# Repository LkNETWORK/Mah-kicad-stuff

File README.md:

# Mah-kicad-stuff
mah kicad shi

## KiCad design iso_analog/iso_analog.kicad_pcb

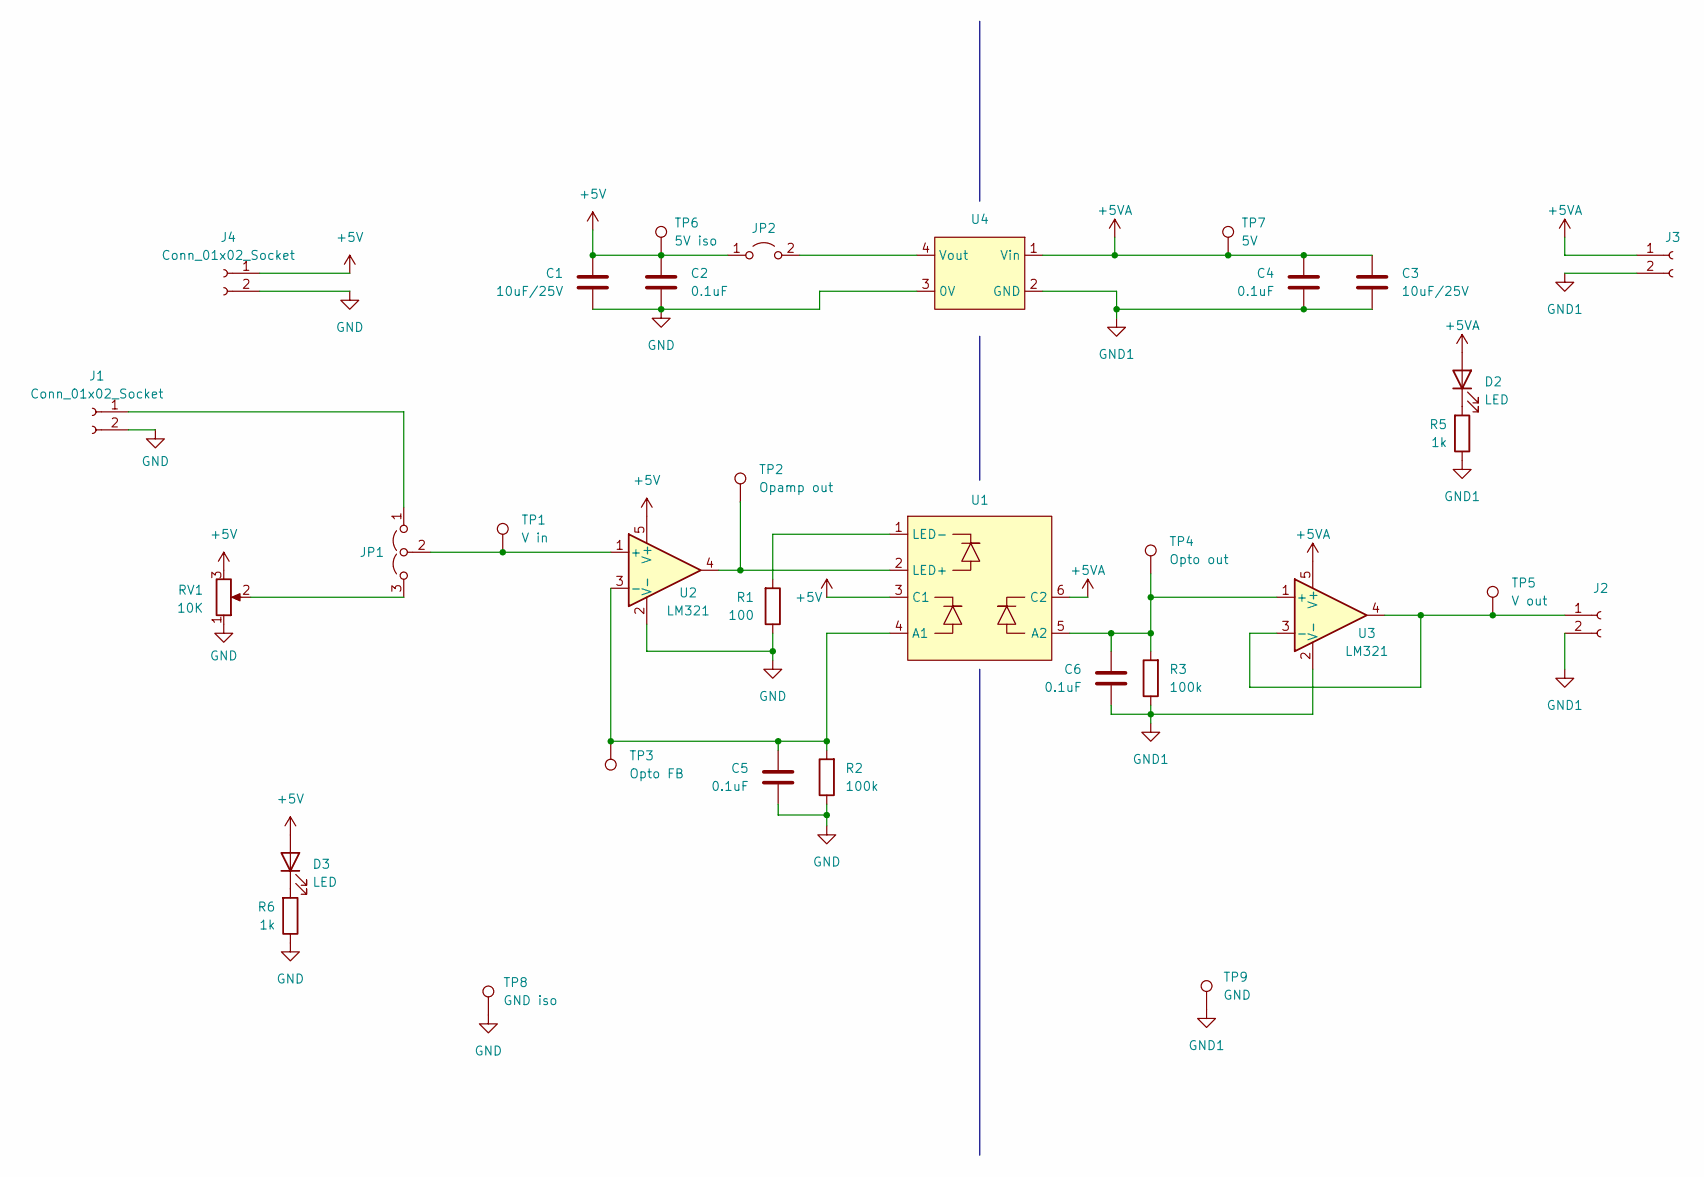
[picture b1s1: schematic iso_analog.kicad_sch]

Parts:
C1, C3: 10uF/25V; C_0805_2012Metric_Pad1.18x1.45mm_HandSolder_L
C2, C4, C5, C6: 0.1uF; C_0805_2012Metric_Pad1.18x1.45mm_HandSolder_L
D2, D3: LED; LED_0805_2012Metric_Pad1.45x1.40mm_HandSolder
J1, J2, J3, J4: Conn_01x02_Socket; PinHeader_1x02_P2.54mm_Vertical
JP1: Jumper_3_Open; SolderJumper-3_P1.3mm_Open_Pad1.0x1.5mm
JP2: Jumper_2_Open; SolderJumper-2_P1.3mm_Open_Pad1.0x1.5mm
R1: 100; R_0805_2012Metric_Pad1.20x1.40mm_HandSolder_L
R2, R3: 100k; R_0805_2012Metric_Pad1.20x1.40mm_HandSolder_L
R5, R6: 1k; R_0805_2012Metric_Pad1.20x1.40mm_HandSolder_L
RV1: 10K; BOURNS-3362P_pot
TP1: V in; PinHeader_1x01_P2.54mm_Vertical
TP2: Opamp out; TestPoint_Pad_D2.0mm
TP3: Opto FB; TestPoint_Pad_D2.0mm
TP4: Opto out; PinHeader_1x01_P2.54mm_Vertical
TP5: V out; TestPoint_Pad_D2.0mm
TP6: 5V iso; TestPoint_Pad_D2.0mm
TP7: 5V; TestPoint_Pad_D2.0mm
TP8: GND iso; PinHeader_1x01_P2.54mm_Vertical
TP9: GND; PinHeader_1x01_P2.54mm_Vertical
U1: LOC110P
U2, U3: LM321; SOT-23-5_HandSoldering
U4: B0505MT-1WR4

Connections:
+5V: C1.1, C2.1, D3.2 (A), J4.1, JP2.1 (A), RV1.3, TP6.1, U1.3 (C1), U2.5 (V+)
+5VA: C3.1, C4.1, D2.2 (A), J3.1, TP7.1, U1.6 (C2), U3.5 (V+), U4.1 (Vin)
GND: C1.2, C2.2, C5.2, J1.2, J4.2, R1.1, R2.1, R6.1, RV1.1, TP8.1, U2.2 (V-), U4.3 (0V)
GND1: C3.2, C4.2, C6.2, J2.2, J3.2, R3.1, R5.1, TP9.1, U3.2 (V-), U4.2 (GND)
unnamed: D2.1 (K), R5.2
unnamed: D3.1 (K), R6.2
unnamed: J1.1, JP1.1 (A)
unnamed: J2.1, TP5.1, U3.3 (-), U3.4
unnamed: JP1.3 (B), RV1.2
unnamed: JP1.2 (C), TP1.1, U2.1 (+)
unnamed: JP2.2 (B), U4.4 (Vout)
unnamed: C5.1, R2.2, TP3.1, U1.4 (A1), U2.3 (-)
unnamed: C6.1, R3.2, TP4.1, U1.5 (A2), U3.1 (+)
unnamed: TP2.1, U1.2 (LED+), U2.4
unnamed: R1.2, U1.1 (LED-)

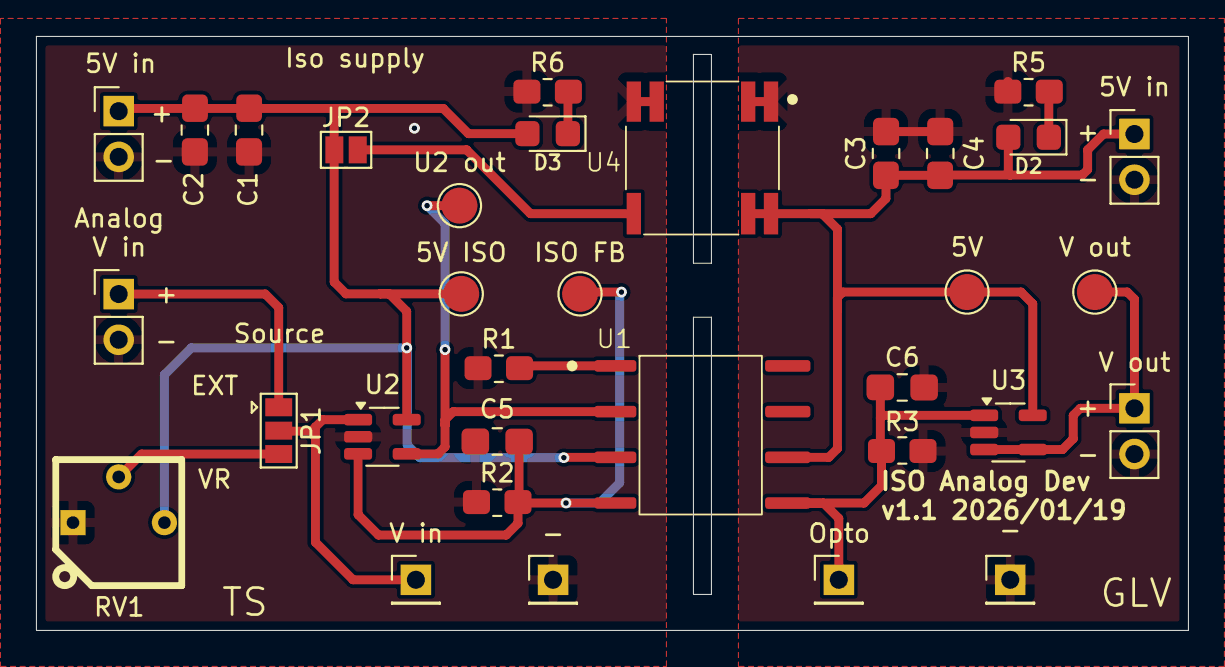
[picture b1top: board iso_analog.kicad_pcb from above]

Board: 2 copper layers, 64.0 x 33.0 mm, 33 parts (0 on the bottom side), 15 nets.

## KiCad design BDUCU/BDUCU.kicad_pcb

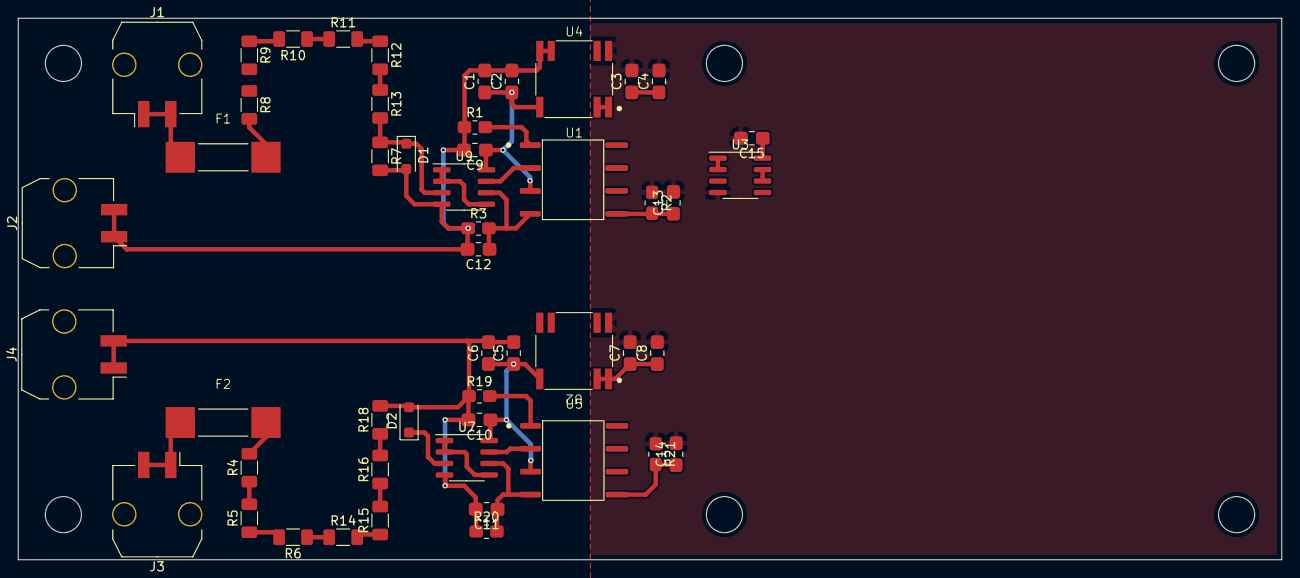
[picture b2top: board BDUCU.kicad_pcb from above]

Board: 2 copper layers, 139.9 x 60.0 mm, 50 parts (0 on the bottom side), 34 nets.

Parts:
C1, C4, C5, C8: 10uF/25V; C_0805_2012Metric_Pad1.18x1.45mm_HandSolder_L
C2, C3, C6, C7, C9, C10, C11, C12, C13, C14, C15: 0.1uF; C_0805_2012Metric_Pad1.18x1.45mm_HandSolder_L
D1, D2: BZT52B5V1; D_SOD-123F
F1, F2: Fuse; LittleFuse_462
J1, J2, J3, J4: Conn_01x02_Pin; Molex_Micro-Fit_3.0_43650-0210_1x02-1MP_P3.00mm_Horizontal
R1, R19: 1k; R_0805_2012Metric_Pad1.20x1.40mm_HandSolder_L
R2, R3, R20, R21: 10k; R_0805_2012Metric_Pad1.20x1.40mm_HandSolder_L
R4, R5, R6, R8, R9, R10, R11, R12, R13, R14, R15, R16: 210k; R_1206_3216Metric_Pad1.30x1.75mm_HandSolder
R7, R18: 10k; R_1206_3216Metric_Pad1.30x1.75mm_HandSolder
U1, U5: LOC110P
U2, U4: B0505MT-1WR4
U3, U7, U9: LM358; SOIC-8_3.9x4.9mm_P1.27mm

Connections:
+5V: C3.1, C4.1, C7.1, C8.1, C15.1, U1.6 (C2), U2.1 (Vin), U3.8 (V+), U4.1 (Vin), U5.6 (C2)
+5VL: C5.1, C6.1, C10.1, U2.4 (Vout), U5.3 (C1), U7.8 (V+)
+5VP: C1.1, C2.1, C9.1, U1.3 (C1), U4.4 (Vout), U9.8 (V+)
AC+: F1.1, R8.2
AC-: C1.2, C2.2, C9.2, C12.2, D1.2 (A), J2.1, J2.2, R1.1, R3.1, R7.2, U4.3 (0V), U9.4 (V-)
AC_ISO: U3.1, U3.2 (-)
GND: C3.2, C4.2, C7.2, C8.2, C13.2, C14.2, C15.2, R2.1, R21.1, U2.2 (GND), U3.4 (V-), U4.2 (GND)
unnamed: D1.1 (K), R7.1, R13.2, U9.3 (+)
unnamed: D2.1 (K), R16.2, R18.1, U7.3 (+)
unnamed: F1.2, J1.1, J1.2
unnamed: F2.2, J3.1, J3.2
unnamed: R4.1, R5.2
unnamed: R5.1, R6.2
unnamed: R8.1, R9.2
unnamed: R10.1, R11.1
unnamed: R9.1, R10.2
unnamed: R11.2, R12.1
unnamed: R12.2, R13.1
unnamed: R6.1, R14.1
unnamed: R14.2, R15.1
unnamed: R15.2, R16.1
unnamed: C12.1, R3.2, U1.4 (A1), U9.6 (-)
unnamed: C13.1, R2.2, U1.5 (A2), U3.3 (+)
unnamed: U1.2 (LED+), U9.7
unnamed: R1.2, U1.1 (LED-)
unnamed: C14.1, R21.2, U3.5 (+), U5.5 (A2)
unnamed: C11.1, R20.2, U5.4 (A1), U7.6 (-)
unnamed: U5.2 (LED+), U7.7
unnamed: R19.2, U5.1 (LED-)
unnamed: U7.1, U7.2 (-), U7.5 (+)
unnamed: U9.1, U9.2 (-), U9.5 (+)
TS+: F2.1, R4.2
TS-: C5.2, C6.2, C10.2, C11.2, D2.2 (A), J4.1, J4.2, R18.2, R19.1, R20.1, U2.3 (0V), U7.4 (V-)
TS_ISO: U3.6 (-), U3.7

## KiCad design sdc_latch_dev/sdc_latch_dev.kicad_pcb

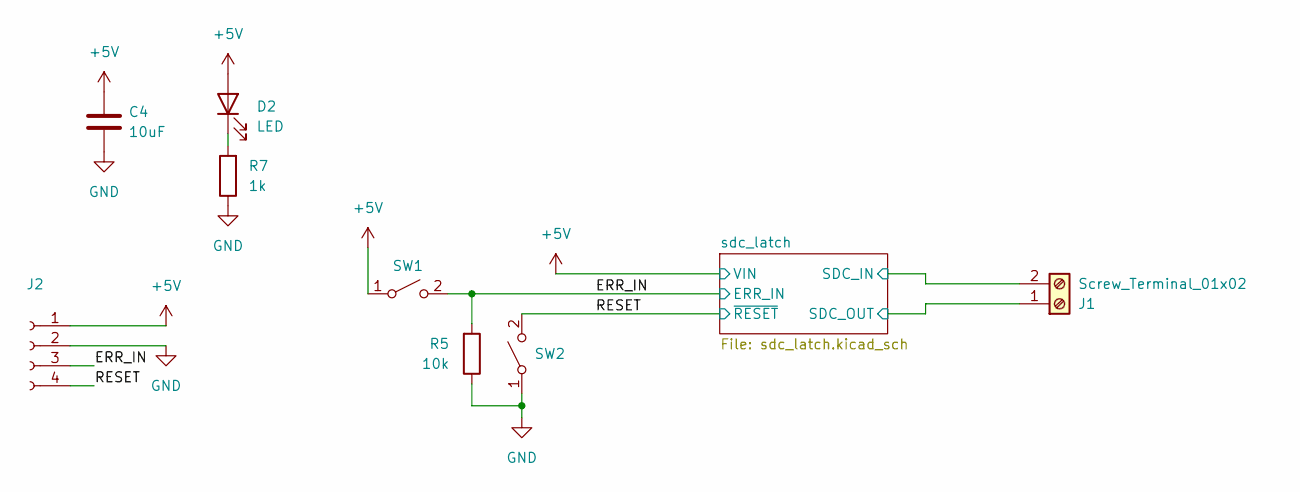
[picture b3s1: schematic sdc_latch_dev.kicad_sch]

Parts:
C4: 10uF; C_0805_2012Metric_Pad1.18x1.45mm_HandSolder_L
D2: LED; LED_0805_2012Metric_Pad1.15x1.40mm_HandSolder
J1: Screw_Terminal_01x02; TerminalBlock_Phoenix_MKDS-1,5-2_1x02_P5.00mm_Horizontal
J2: Conn_01x04_Socket; PinHeader_1x04_P2.54mm_Vertical
R5: 10k; R_0805_2012Metric_Pad1.20x1.40mm_HandSolder_L
R7: 1k; R_0805_2012Metric_Pad1.20x1.40mm_HandSolder_L
SW1, SW2: SW_SPST; SW_PUSH_6mm_H13mm

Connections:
+5V: C4.1, D2.2 (A), J2.1, SW1.1 (A); also elsewhere on the board
/ERR_IN: J2.3, R5.2, SW1.2 (B); also elsewhere on the board
/RESET: J2.4, SW2.2 (B); also elsewhere on the board
/sdc_latch/SDC_IN: J1.2; also elsewhere on the board
/sdc_latch/SDC_OUT: J1.1; also elsewhere on the board
GND: C4.2, J2.2, R5.1, R7.1, SW2.1 (A); also elsewhere on the board
unnamed: D2.1 (K), R7.2

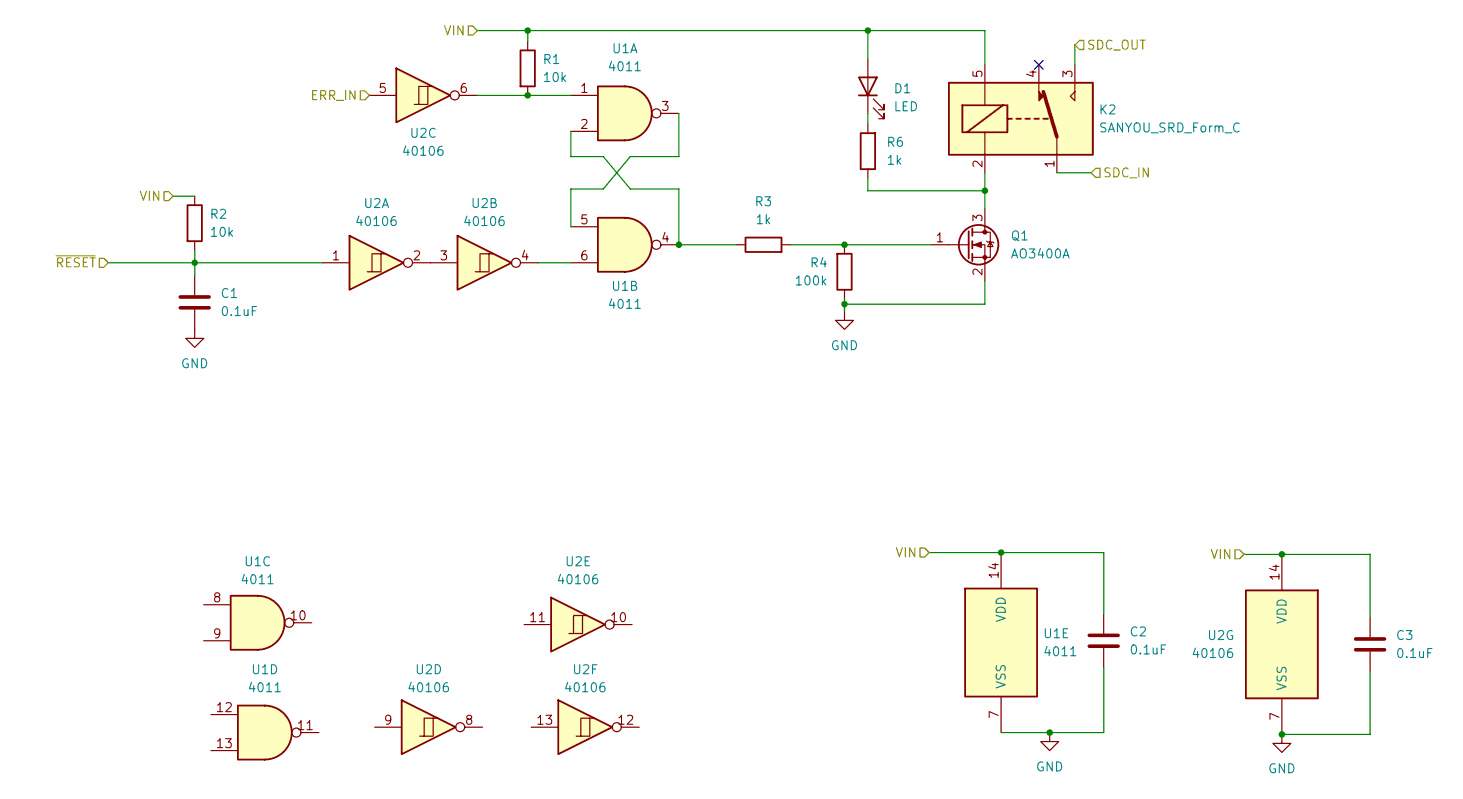
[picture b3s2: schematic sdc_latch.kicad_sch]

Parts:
C1, C2, C3: 0.1uF; C_0805_2012Metric_Pad1.18x1.45mm_HandSolder_L
D1: LED; LED_0805_2012Metric_Pad1.15x1.40mm_HandSolder
K2: SANYOU_SRD_Form_C; Relay_SPDT_SANYOU_SRD_Series_Form_C
Q1: AO3400A; SOT-23_Handsoldering
R1, R2: 10k; R_0805_2012Metric_Pad1.20x1.40mm_HandSolder_L
R3, R6: 1k; R_0805_2012Metric_Pad1.20x1.40mm_HandSolder_L
R4: 100k; R_0805_2012Metric_Pad1.20x1.40mm_HandSolder_L
U1: 4011; SOIC-14_3.9x8.7mm_P1.27mm
U2: 40106; SOIC-14_3.9x8.7mm_P1.27mm

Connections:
+5V: C2.1, C3.1, D1.2 (A), K2.5, R1.1, R2.1, U1.14 (VDD), U2.14 (VDD); also elsewhere on the board
/ERR_IN: U2.5; also elsewhere on the board
/RESET: C1.1, R2.2, U2.1; also elsewhere on the board
/sdc_latch/SDC_IN: K2.1; also elsewhere on the board
/sdc_latch/SDC_OUT: K2.3; also elsewhere on the board
GND: C1.2, C2.2, C3.2, Q1.2 (S), R4.1, U1.7 (VSS), U2.7 (VSS); also elsewhere on the board
unnamed: D1.1 (K), R6.2
unnamed: K2.2, Q1.3 (D), R6.1
unnamed: Q1.1 (G), R3.2, R4.2
unnamed: R1.2, U1.1, U2.6
unnamed: R3.1, U1.2, U1.4
unnamed: U1.3, U1.5
unnamed: U1.6, U2.4
unnamed: U2.2, U2.3

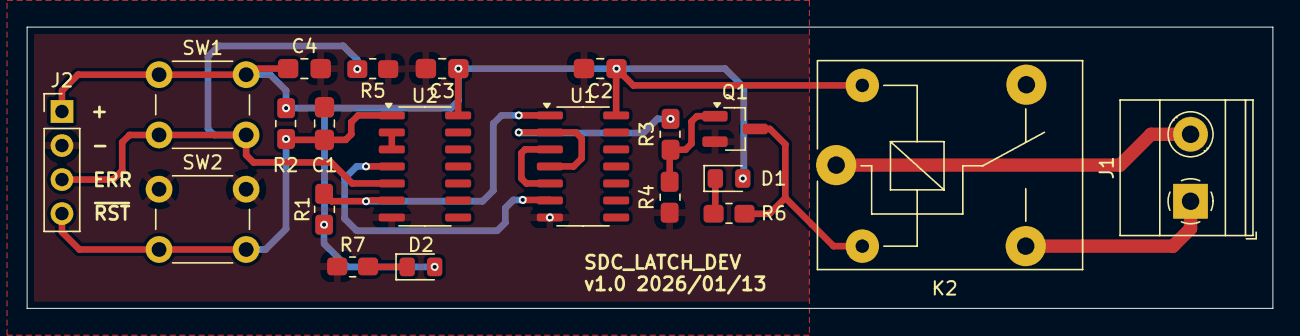
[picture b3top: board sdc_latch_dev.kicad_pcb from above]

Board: 2 copper layers, 93.0 x 21.0 mm, 21 parts (0 on the bottom side), 15 nets.

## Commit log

2026-01-13 new git ignore
2026-01-13 initial push trash
2026-02-18 start doing bducu
2026-03-22 iso analog update stuff
